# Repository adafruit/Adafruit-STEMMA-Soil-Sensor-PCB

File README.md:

## Adafruit STEMMA Soil Sensor - I2C Capacitive Moisture Sensor PCB

<a href="http://www.adafruit.com/products/4026"><br/>
Click here to purchase one from the Adafruit shop</a>

PCB files for the Adafruit STEMMA Soil Sensor - I2C Capacitive Moisture Sensor. Format is EagleCAD schematic and board layout
* https://www.adafruit.com/product/4026

### Description

Most low cost soil sensors are resistive style, where there's two prongs and the sensor measures the conductivity between the two. These work OK at first, but eventually start to oxidize because of the exposed metal. Even if they're gold plated! The resistivity measurement goes up and up, so you constantly have to re-calibrate your code. Also, resistive measurements don't always work in loose soil.

This design is superior with a **capacitive** measurement. Capacitive measurements use only one probe, don't have any exposed metal, and don't introduce any DC currents into your plants. We use the built in capacitive touch measurement system built into the ATSAMD10 chip, which will give you a reading ranging from about 200 (very dry) to 2000 (very wet). As a bonus, we also give you the ambient temperature from the internal temperature sensor on the microcontroller, it's not high precision, maybe good to + or - 2 degrees Celsius.

To make it so you can use the sensor with just about any microcontroller, we have an I2C interface. Connect a 4-pin JST-PH cable (we have a few stocked) to your microcontroller or single board computer to 3-5V power, Ground, I2C SDA and I2C SCL and [then run our Arduino or CircuitPython code to read the temperature and capacitive measurement](https://learn.adafruit.com/adafruit-stemma-soil-sensor-i2c-capacitive-moisture-sensor). No soldering required!

**Please note: This is just the sensor, you'll also need a JST 4-PH cable to go along for plugging it in!** We have a few options such as one with [male header pins](https://www.adafruit.com/product/3955), [female header pins](https://www.adafruit.com/product/3950), and a [JST-JST cable](https://www.adafruit.com/product/3568). You can use Seeed Grove cables and boards to connect - the Grove cable is a little different looking but will fit just fine.

[Check out the full guide for schematics, wiring, code and more!](https://learn.adafruit.com/adafruit-stemma-soil-sensor-i2c-capacitive-moisture-sensor)

### License

Adafruit invests time and resources providing this open source design, please support Adafruit and open-source hardware by purchasing products from [Adafruit](https://www.adafruit.com)!

Designed by Limor Fried/Ladyada for Adafruit Industries.

Creative Commons Attribution/Share-Alike, all text above must be included in any redistribution. See license.txt for additional details.

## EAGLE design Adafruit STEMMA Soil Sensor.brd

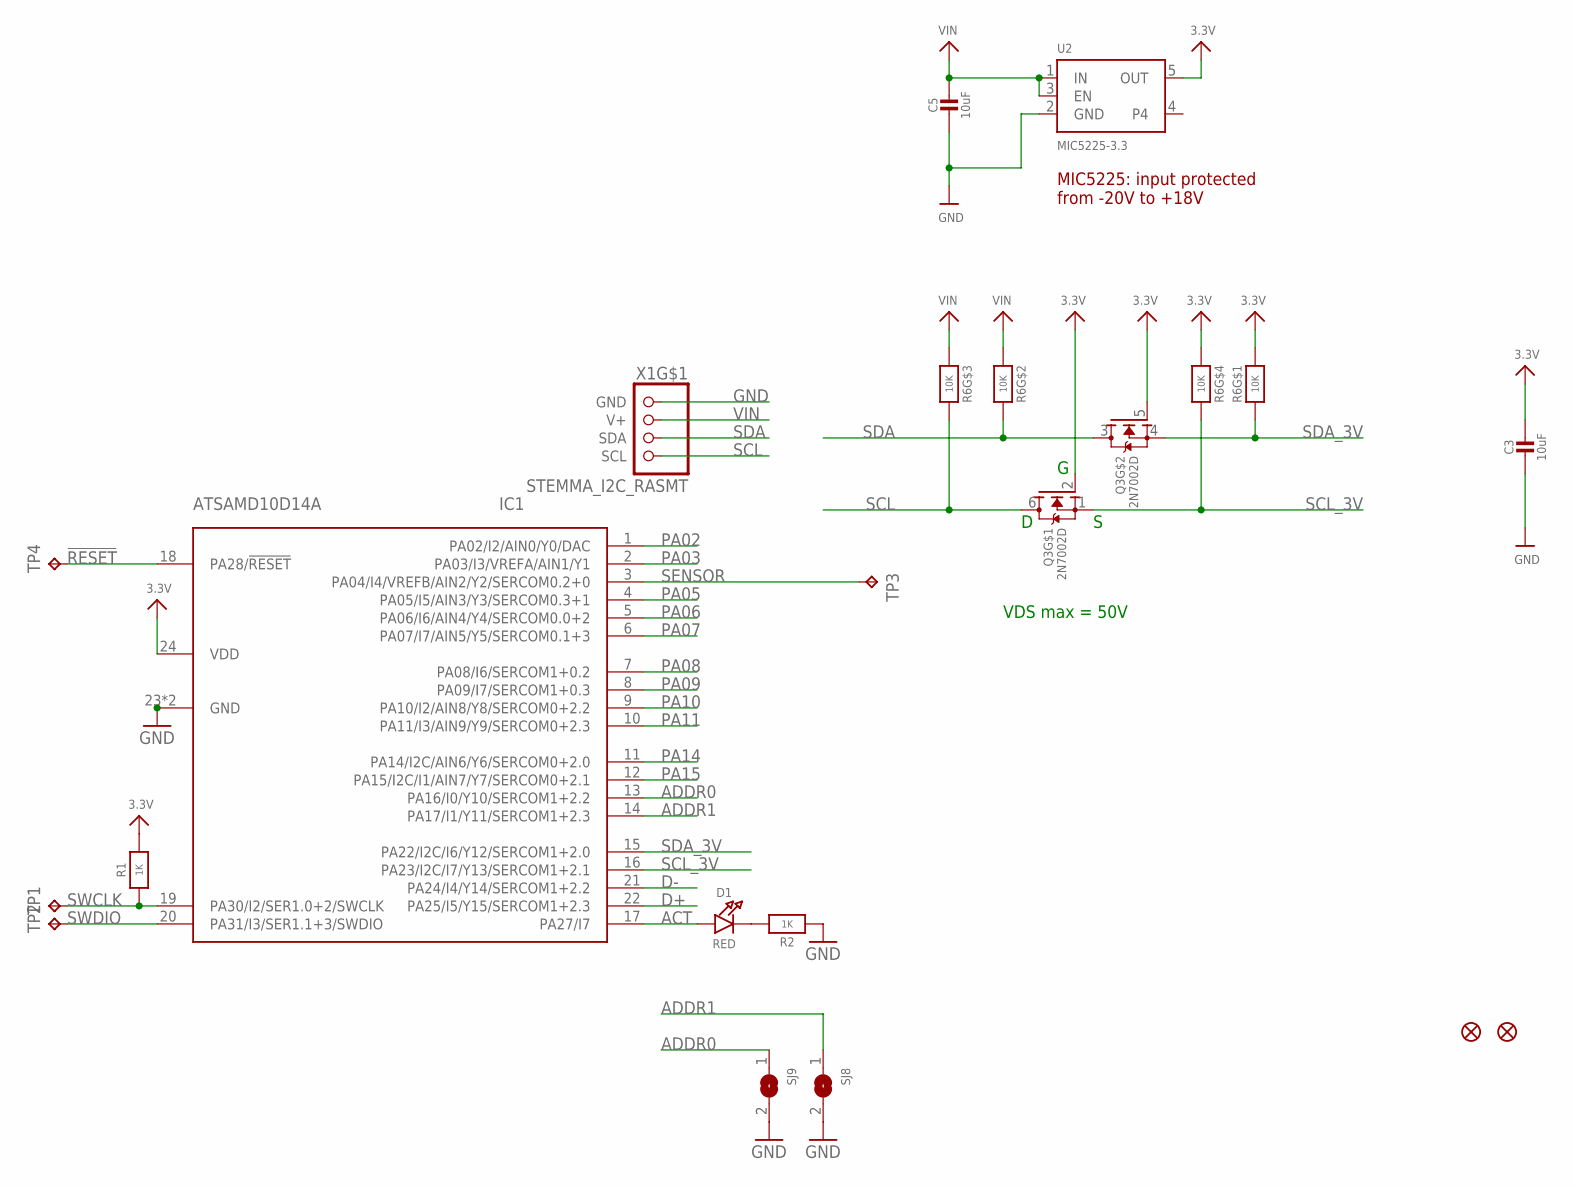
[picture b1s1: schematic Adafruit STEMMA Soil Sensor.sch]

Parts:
C3, C5: 10uF; 0805-NO
D1: RED; CHIPLED_0805_NOOUTLINE
FID1, FID2: FIDUCIAL_1MM
IC1: ATSAMD10D14A; QFN24_4MM
Q3: 2N7002D; SOT363
R1, R2: 1K; 0603-NO
R6: 10K; RESPACK_4X0603
SJ8, SJ9: SOLDERJUMPER; SOLDERJUMPER_ARROW_NOPASTE
TP1, TP2, TP4: TPTP15R; TP15R
TP3: TPTP10R; TP10R
U2: MIC5225-3.3; SOT23-5
X1: STEMMA_I2C_RASMT; JSTPH4

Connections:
3.3V: C3.1, IC1.24 (VDD), Q3.2 (G), Q3.5 (G), R1.2, R6.1, R6.5 (2), U2.5 (OUT)
!RESET: IC1.18 (PA28/!RESET), TP4.TP
ACT: D1.A, IC1.17 (PA27/I7)
ADDR0: IC1.13 (PA16/I0/Y10/SERCOM1+2.2), SJ9.1
ADDR1: IC1.14 (PA17/I1/Y11/SERCOM1+2.3), SJ8.1
D+: IC1.22 (PA25/I5/Y15/SERCOM1+2.3)
D-: IC1.21 (PA24/I4/Y14/SERCOM1+2.2)
GND: C3.2, C5.2, IC1.23 (GND), IC1.THERM (GND), R2.1, SJ8.2, SJ9.2, U2.2 (GND), X1.1 (GND)
unnamed: D1.C, R2.2
PA02: IC1.1 (PA02/I2/AIN0/Y0/DAC)
PA03: IC1.2 (PA03/I3/VREFA/AIN1/Y1)
PA05: IC1.4 (PA05/I5/AIN3/Y3/SERCOM0.3+1)
PA06: IC1.5 (PA06/I6/AIN4/Y4/SERCOM0.0+2)
PA07: IC1.6 (PA07/I7/AIN5/Y5/SERCOM0.1+3)
PA08: IC1.7 (PA08/I6/SERCOM1+0.2)
PA09: IC1.8 (PA09/I7/SERCOM1+0.3)
PA10: IC1.9 (PA10/I2/AIN8/Y8/SERCOM0+2.2)
PA11: IC1.10 (PA11/I3/AIN9/Y9/SERCOM0+2.3)
PA14: IC1.11 (PA14/I2C/AIN6/Y6/SERCOM0+2.0)
PA15: IC1.12 (PA15/I2C/I1/AIN7/Y7/SERCOM0+2.1)
SCL: Q3.6 (D), R6.6 (2), X1.4 (SCL)
SCL_3V: IC1.16 (PA23/I2C/I7/Y13/SERCOM1+2.1), Q3.1 (S), R6.4 (1)
SDA: Q3.3 (D), R6.7 (2), X1.3 (SDA)
SDA_3V: IC1.15 (PA22/I2C/I6/Y12/SERCOM1+2.0), Q3.4 (S), R6.8 (2)
SENSOR: IC1.3 (PA04/I4/VREFB/AIN2/Y2/SERCOM0.2+0), TP3.TP
SWCLK: IC1.19 (PA30/I2/SER1.0+2/SWCLK), R1.1, TP1.TP
SWDIO: IC1.20 (PA31/I3/SER1.1+3/SWDIO), TP2.TP
VIN: C5.1, R6.2 (1), R6.3 (1), U2.1 (IN), U2.3 (EN), X1.2 (V+)

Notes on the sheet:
MIC5225: input protected from -20V to +18V
VDS max = 50V

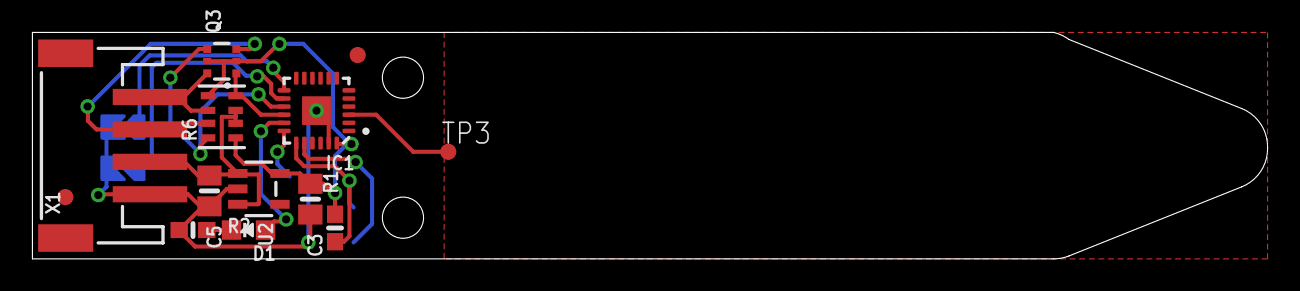
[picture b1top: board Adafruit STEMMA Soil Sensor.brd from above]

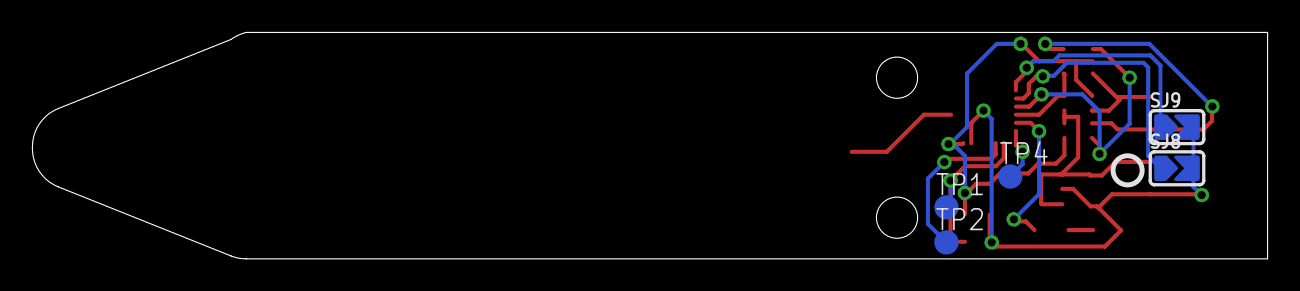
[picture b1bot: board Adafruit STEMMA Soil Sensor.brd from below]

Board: 2 copper layers, 76.2 x 14.0 mm, 21 parts (7 on the bottom side), 15 nets.

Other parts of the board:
U$4: STEMMA_SOIL_BOT
U$5: STEMMA_SOIL_TOP
U$12: PCBFEAT-REV-040

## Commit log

2018-11-14 init
2019-07-16 updated to use cookiecutter for pcb repos

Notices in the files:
parts and their libraries:
microbuilder: This work is placed in the public domain, and may be freely used for commercial and non-commercial work with the following conditions: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
